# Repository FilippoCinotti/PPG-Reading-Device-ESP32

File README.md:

# FireBeetle ESP32 IoT Microcontroller - PPG reading device

Project description here:
https://my.visme.co/projects/rxyojmyo-bioe-cs-494-2#s1

PPG signal:

User Interface:

Final device:

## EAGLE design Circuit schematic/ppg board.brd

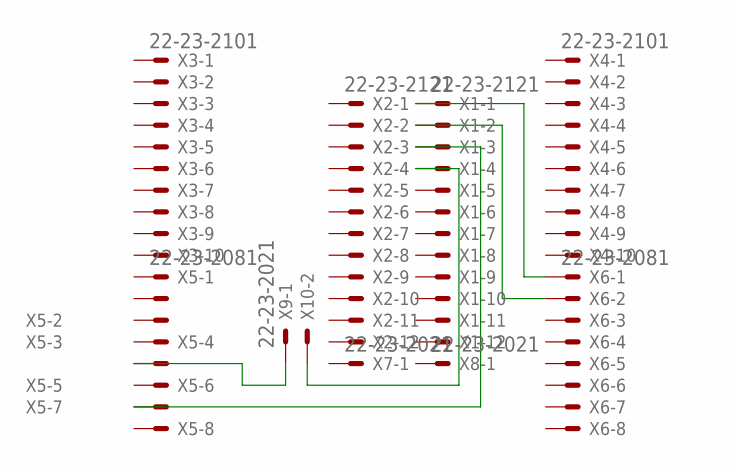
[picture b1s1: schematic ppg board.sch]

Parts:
X1, X2: 22-23-2121
X3, X4: 22-23-2101
X5, X6: 22-23-2081
X7, X8, X9, X10: 22-23-2021

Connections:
unnamed: X1.2, X6.2
unnamed: X5.5, X9.1
unnamed: X1.1, X6.1
unnamed: X1.3, X5.7
unnamed: X1.4, X10.2

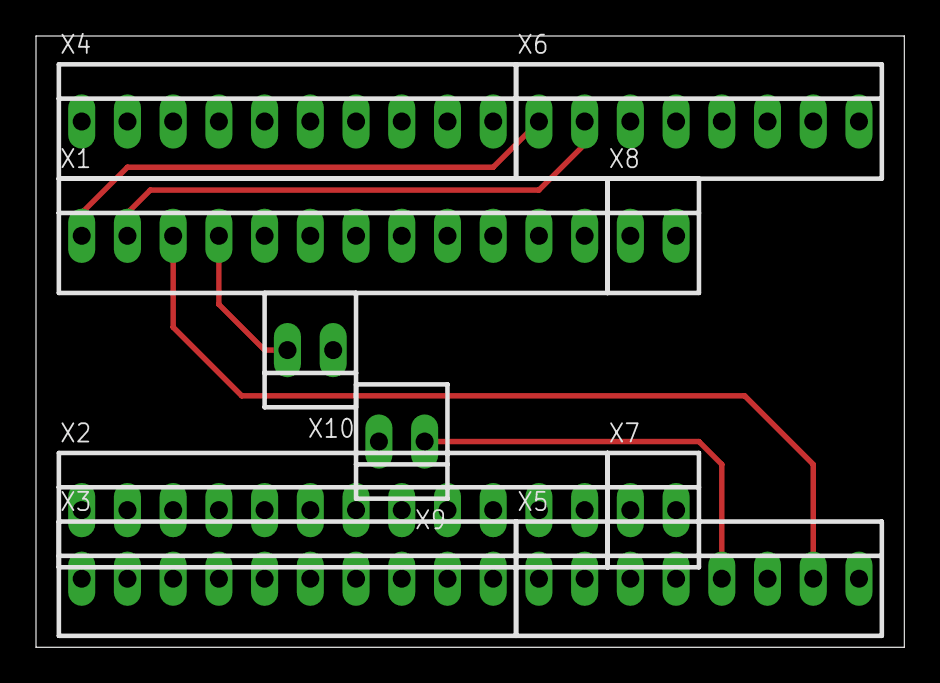
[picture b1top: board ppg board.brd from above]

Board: 2 copper layers, 48.2 x 34.0 mm, 10 parts (0 on the bottom side), 5 nets.
